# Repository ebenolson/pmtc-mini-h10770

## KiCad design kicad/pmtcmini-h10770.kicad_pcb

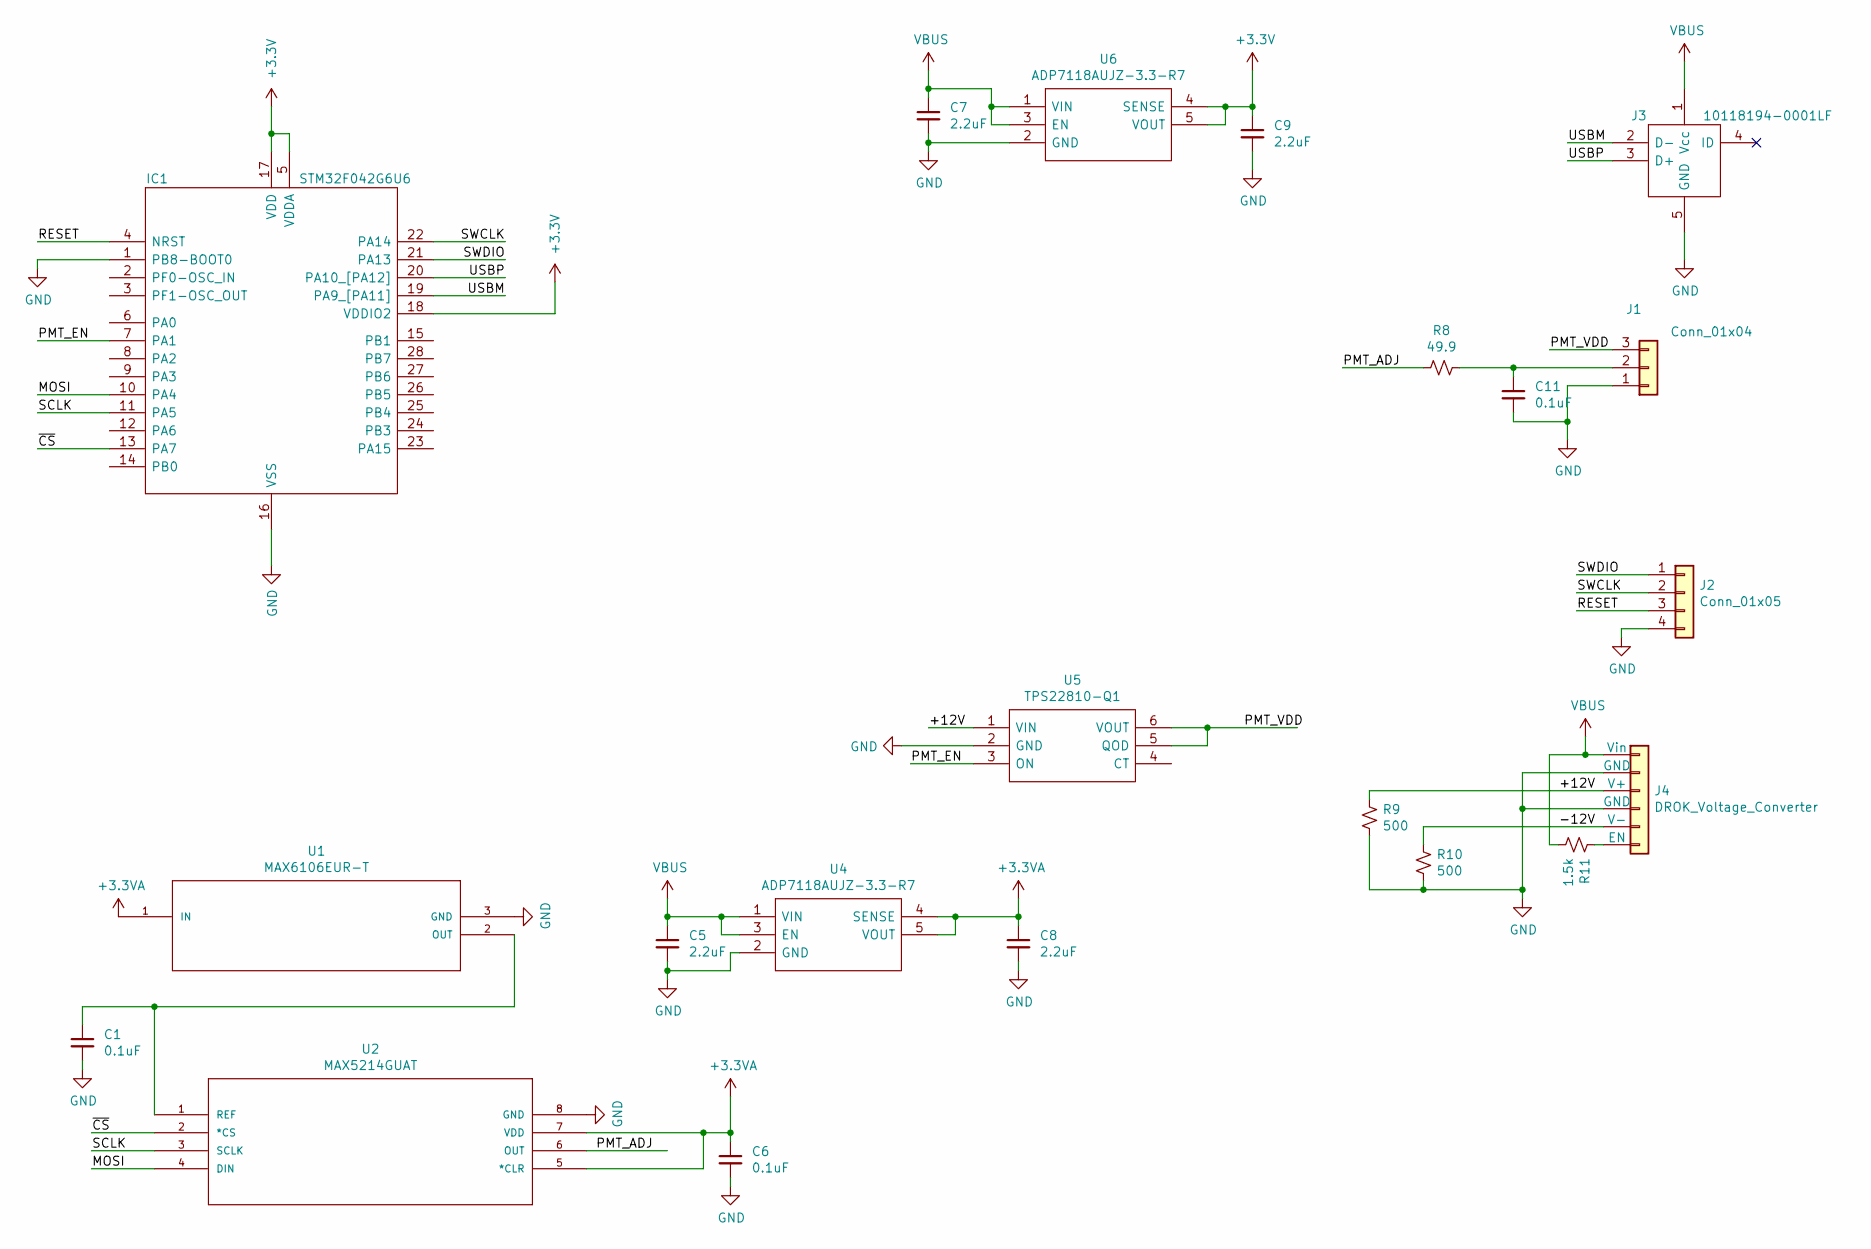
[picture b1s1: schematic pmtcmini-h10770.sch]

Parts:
C1, C6, C11: 0.1uF; C_0603_1608Metric
C5, C7, C8, C9: 2.2uF; C_0603_1608Metric
IC1: STM32F042G6U6; QFN50P400X400X60-28N; Manufacturer_Part_Number STM32F042G6U6; Mouser Part Number 511-STM32F042G6U6
J1: Conn_01x04; PinHeader_1x03_P2.54mm_Vertical
J2: Conn_01x05; POGO_ISP
J3: 10118194-0001LF; USB_Micro_B_Female_10118194-0001LF
J4: DROK_Voltage_Converter
R8: 49.9; R_0603_1608Metric
R9, R10: 500; R_1206_3216Metric
R11: 1.5k; R_0603_1608Metric
U1: MAX6106EUR-T; 21-0051H
U2: MAX5214GUAT; 21-0036K
U4, U6: ADP7118AUJZ-3.3-R7; SOT95P280X100-5N; Manufacturer_Part_Number ADP7118AUJZ-3.3-R7
U5: TPS22810-Q1; SOT95P280X100-6N; Manufacturer_Part_Number TPS22810-Q1

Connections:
+3.3VA: C6.1, C8.1, U1.1 (IN), U2.5 (*CLR), U2.7 (VDD), U4.4 (SENSE), U4.5 (VOUT)
+3V3: C9.1, IC1.5 (VDDA), IC1.17 (VDD), IC1.18 (VDDIO2), U6.4 (SENSE), U6.5 (VOUT)
/+12V: J4.3 (V+), R9.2, U5.1 (VIN)
/-12V: J4.5 (V-), R10.2
/MOSI: IC1.10 (PA4), U2.4 (DIN)
/PMT_ADJ: R8.2, U2.6 (OUT)
/PMT_EN: IC1.7 (PA1), U5.3 (ON)
/PMT_VDD: J1.3, U5.5 (QOD), U5.6 (VOUT)
/RESET: IC1.4 (NRST), J2.3
/SCLK: IC1.11 (PA5), U2.3 (SCLK)
/SWCLK: IC1.22 (PA14), J2.2
/SWDIO: IC1.21 (PA13), J2.1
/USBM: IC1.19 (PA9_[PA11]), J3.2 (D-)
/USBP: IC1.20 (PA10_[PA12]), J3.3 (D+)
/~CS: IC1.13 (PA7), U2.2 (*CS)
GND: C1.2, C5.2, C6.2, C7.2, C8.2, C9.2, C11.2, IC1.1 (PB8-BOOT0), IC1.16 (VSS), J1.1, J2.4, J3.5 (GND), J4.2 (GND), J4.4 (GND), R9.1, R10.1, U1.3 (GND), U2.8 (GND), U4.2 (GND), U5.2 (GND), U6.2 (GND)
unnamed: C1.1, U1.2 (OUT), U2.1 (REF)
unnamed: C11.1, J1.2, R8.1
unnamed: J4.6 (EN), R11.2
VBUS: C5.1, C7.1, J3.1 (Vcc), J4.1 (Vin), R11.1, U4.1 (VIN), U4.3 (EN), U6.1 (VIN), U6.3 (EN)

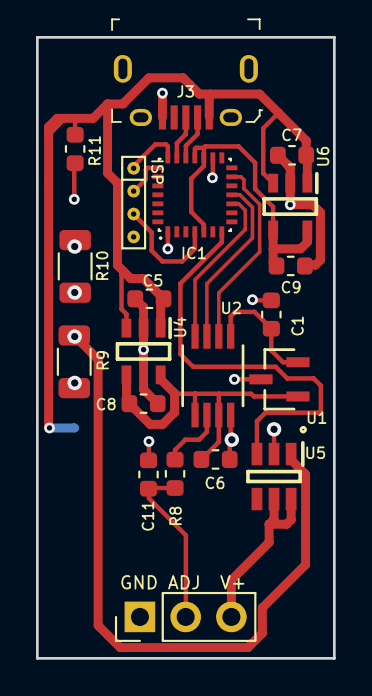
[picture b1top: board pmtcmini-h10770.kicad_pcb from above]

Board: 2 copper layers, 16.5 x 34.5 mm, 21 parts (1 on the bottom side), 20 nets.

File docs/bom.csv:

"Id";"Designator";"Package";"Quantity";"Designation";"Supplier and ref";
1;"C6,C11,C1";"C_0603_1608Metric";3;"0.1uF";;;
2;"U2";"21-0036K";1;"MAX5214GUAT";;;
3;"REF**,REF**,REF**,REF**";"MountingHole_2.2mm_M2";4;"MountingHole_2.2mm_M2";;;
4;"U5";"SOT95P280X100-6N";1;"TPS22810-Q1";;;
5;"U1";"21-0051H";1;"MAX6106EUR-T";;;
6;"J1";"PinHeader_1x03_P2.54mm_Vertical";1;"Conn_01x04";;;
7;"J4";"DROK_Voltage_Converter";1;"DROK_Voltage_Converter";;;
8;"R11";"R_0603_1608Metric";1;"1.5k";;;
9;"R10,R9";"R_0805_2012Metric";2;"500";;;
10;"R8";"R_0603_1608Metric";1;"49.9";;;
11;"C9,C8,C7,C5";"C_0603_1608Metric";4;"2.2uF";;;
12;"U6,U4";"SOT95P280X100-5N";2;"ADP7118AUJZ-3.3-R7";;;
13;"J2";"POGO_ISP";1;"Conn_01x05";;;
14;"IC1";"QFN50P400X400X60-28N";1;"STM32F042G6U6";;;
15;"J3";"USB_Micro_B_Female_10118194-0001LF";1;"10118194-0001LF";;;

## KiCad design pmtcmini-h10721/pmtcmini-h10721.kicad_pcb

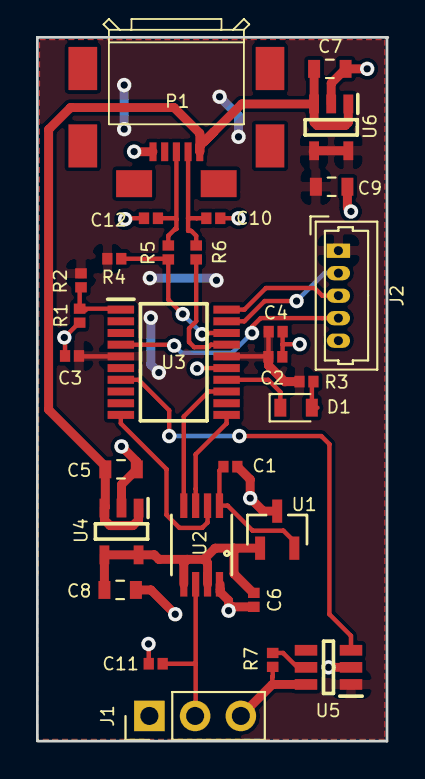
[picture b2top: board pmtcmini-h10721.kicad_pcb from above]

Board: 2 copper layers, 19.5 x 39.1 mm, 29 parts (0 on the bottom side), 23 nets.

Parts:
C1, C3, C4, C6, C11: 0.1uF; C_0402_1005Metric
C2: 1uF; C_0402_1005Metric
C5, C7, C8, C9: 2.2uF; C_0603_1608Metric
C10, C12: 47pF; C_0402_1005Metric
D1: LED; LED_0603_1608Metric
J1: Conn_01x03; PinHeader_1x03_P2.54mm_Vertical
J2: Conn_01x05; Molex_PicoBlade_53047-1010_1x05_P1.25mm_Vertical
P1: ZX62M-B-5P(01); HRS_ZX62M-B-5P(01)
R1, R4: 1.5k; R_0402_1005Metric
R2, R7: 0; R_0402_1005Metric
R3: 330; R_0402_1005Metric
R5, R6: 22; R_0402_1005Metric
U1: MAX6106EUR-T; 21-0051H
U2: MAX5214GUAT; 21-0036K
U3: STM32F042F6P6; SOP65P640X120-20N
U4, U6: ADP7118AUJZ-3.3-R7; SOT95P280X100-5N
U5: TPS22918TDBVTQ1; SOT95P280X100-6N

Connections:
+3.3VA: C6.1, C8.1, U1.1, U2.5, U2.7, U4.4, U4.5
+3V3: C2.1, C3.1, C4.1, C9.1, J2.1, R2.2, R3.1, R4.2, U3.5, U3.16, U5.1, U6.4, U6.5
/LED: D1.1, U3.14
/MOSI: U2.4, U3.13
/PMT_ADJ: C11.1, J1.2, U2.6
/PMT_EN: U3.7, U5.3
/PMT_VDD: J1.3, R7.2, U5.6
/RESET: J2.4, U3.4
/SCLK: U2.3, U3.11
/SWCLK: J2.3, U3.20
/SWDIO: J2.2, U3.19
/USBM: C10.1, P1.2, R6.1
/USBP: C12.1, P1.3, R5.1
/\CS: U2.2, U3.10
GND: C2.2, C3.2, C4.2, C5.2, C7.2, C9.2, C10.2, C11.2, C12.2, J1.1, J2.5, P1.5, R1.2, U3.15, U4.2, U5.2, U6.2
GNDA: C1.2, C6.2, C8.2, U1.3, U2.8
unnamed: C1.1, U1.2, U2.1
unnamed: D1.2, R3.2
unnamed: R1.1, R2.1, U3.1
unnamed: R4.1, R5.2, U3.18
unnamed: R6.2, U3.17
unnamed: R7.1, U5.5
VBUS: C5.1, C7.1, P1.1, U4.1, U4.3, U6.1, U6.3

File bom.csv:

"Id";"Designator";"Package";"Quantity";"Designation";"Supplier and ref";
1;"J2";"Molex_PicoBlade_53047-1010_1x05_P1.25mm_Vertical";1;"Conn_01x05";;;
2;"U2";"21-0036K";1;"MAX5214GUAT";;;
3;"U1";"21-0051H";1;"MAX6106EUR-T";;;
4;"P1";"HRS_ZX62M-B-5P(01)";1;"ZX62M-B-5P(01)";;;
5;"U3";"SOP65P640X120-20N";1;"STM32F042F6P6";;;
6;"U6,U4";"SOT95P280X100-5N";2;"ADP7118AUJZ-3.3-R7";;;
7;"U5";"SOT95P280X100-6N";1;"TPS22918TDBVTQ1";;;
8;"C12,C10";"C_0402_1005Metric";2;"47pF";;;
9;"C11,C6,C4,C3,C1";"C_0402_1005Metric";5;"0.1uF";;;
10;"C2";"C_0402_1005Metric";1;"1uF";;;
11;"C9,C8,C7,C5";"C_0603_1608Metric";4;"2.2uF";;;
12;"J1";"PinHeader_1x03_P2.54mm_Vertical";1;"Conn_01x03";;;
13;"D1";"LED_0603_1608Metric";1;"LED";;;
14;"R7,R2";"R_0402_1005Metric";2;"0";;;
15;"R1,R4";"R_0402_1005Metric";2;"1.5k";;;
16;"R3";"R_0402_1005Metric";1;"330";;;
17;"R5,R6";"R_0402_1005Metric";2;"22";;;

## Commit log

2018-06-25 rev A
2018-06-25 part pos
2018-06-25 assembly drawing
2018-06-25 more plots
2018-07-06 revB sch & pcb
2018-07-06 reorg and cleanup
2018-07-06 reorg
2018-07-06 h10770 revA
2018-07-06 cleanup
2018-07-06 generate fab files
2018-07-09 docs
2019-10-14 rework progress
2021-01-28 revB
2021-01-29 add new case files
2021-01-29 revC, bugfixes
